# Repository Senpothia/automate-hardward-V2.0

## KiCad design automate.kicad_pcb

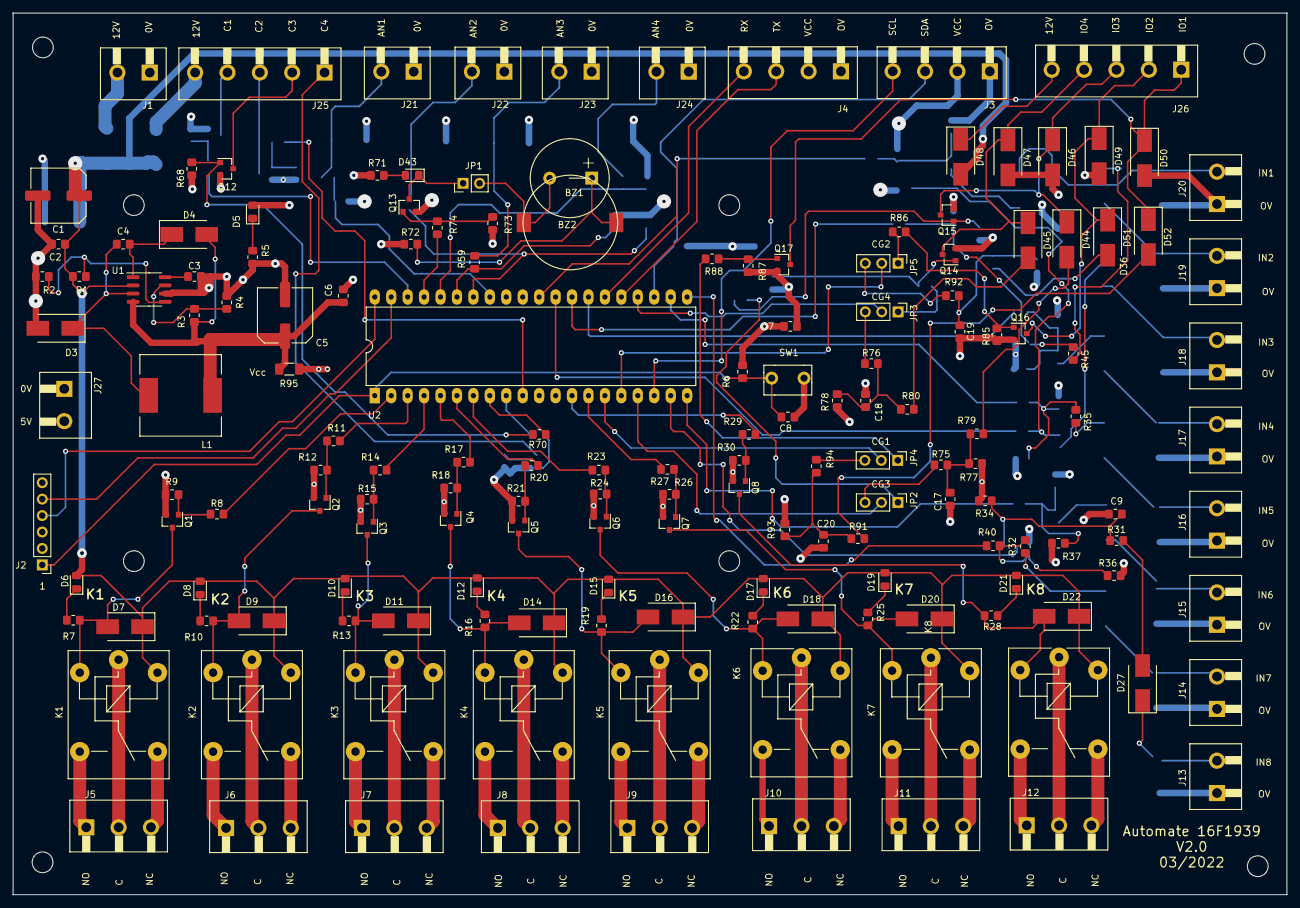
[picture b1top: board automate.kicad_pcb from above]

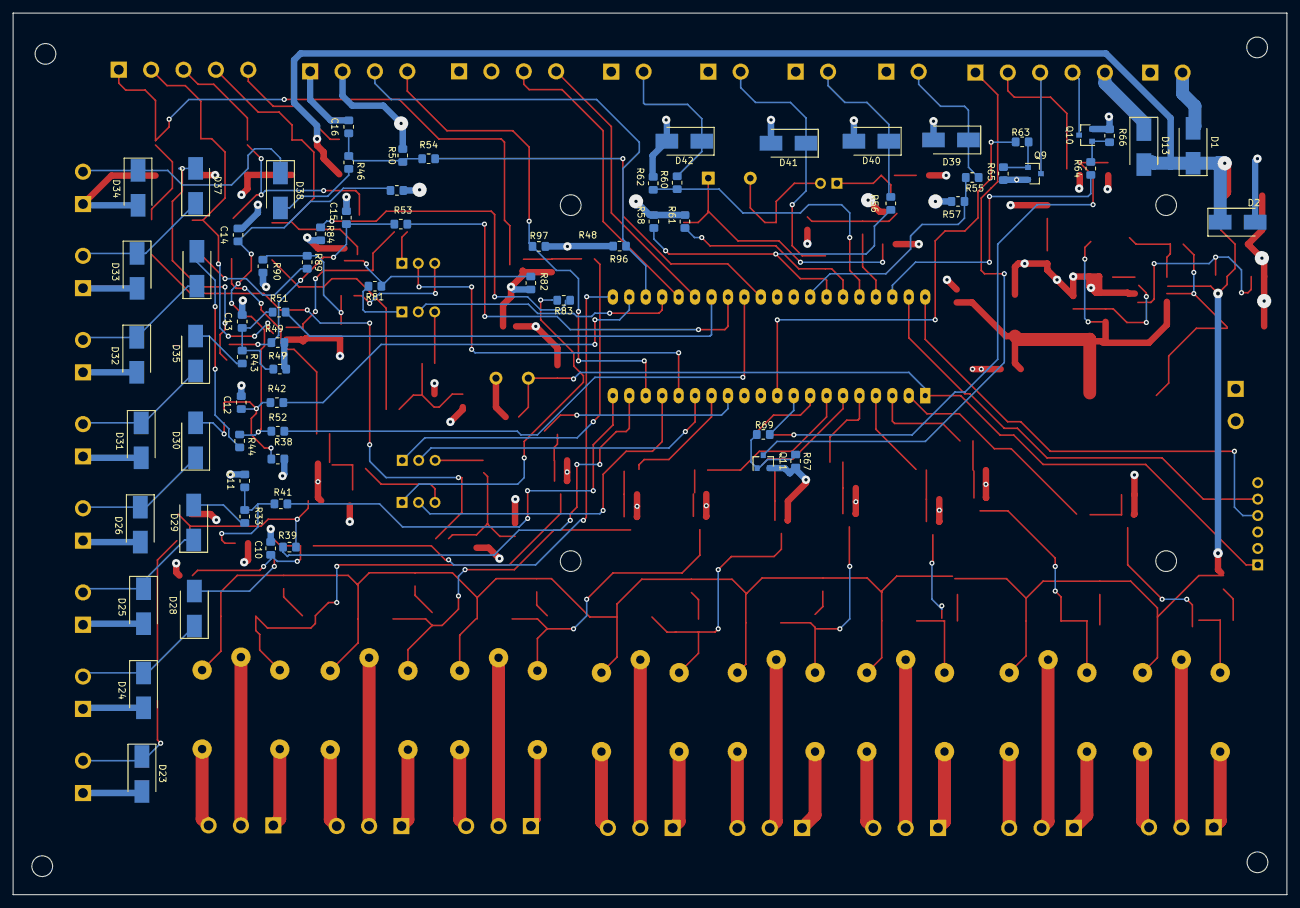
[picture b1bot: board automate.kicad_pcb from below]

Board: 4 copper layers, 196.8 x 136.2 mm, 232 parts (69 on the bottom side), 162 nets.

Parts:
BZ1: Buzzer; Buzzer_Mallory_AST1109MLTRQ
BZ2: Buzzer; Buzzer_12x9.5RM7.6
C1, C5: 100µF; C_Elec_8x6.2
C2, C4, C6, C7, C8, C9, C10, C11, C12, C13, C14, C15, C16, C17, C18, C19, C20: 100nF; R_0805_2012Metric_Pad1.20x1.40mm_HandSolder
C3: 2.2nF; R_0805_2012Metric_Pad1.20x1.40mm_HandSolder
D1, D3, D4, D7, D9, D11, D13, D14, D16, D18, D20, D22, D27, D28, D29, D30, D35, D36, D37, D38, D44, D45, D48, D51, D52: SSA36; D_SMB_SSA36-Handsoldering
D2, D23, D24, D25, D26, D31, D32, D33, D34, D39, D40, D41, D42, D46, D47, D49, D50: SMBJ15A; D_SMB_Handsoldering
D5, D6, D8, D10, D12, D15, D17, D19, D21: LED; D_0805_2012Metric_Pad1.15x1.40mm_HandSolder
D43: LED; LED_0805_2012Metric_Pad1.15x1.40mm_HandSolder
J1, J13, J14, J15, J16, J17, J18, J19, J20, J21, J22, J23, J24, J27: Conn_01x02_Female; conn-2pts-P5mm
J2: Conn_01x06_Female; PinHeader_1x06_P2.54mm_Vertical
J3, J4: Conn_01x04_Female; conn-4pts-P5mm
J5, J6, J7, J8, J9, J10, J11, J12: Conn_01x03_Female; conn-3pts-P5mm
J25, J26: Conn_01x05_Female; conn-5pts-P5mm
JP1: Jumper; PinHeader_1x02_P2.54mm_Vertical
JP2, JP3, JP4, JP5: Jumper_NC_Dual; PinHeader_1x03_P2.54mm_Vertical
K1, K2, K3, K4, K5, K6, K7, K8: SONGLE; Relay_SRD_Series_Form_C
L1: 100µH; L_Wuerth_WE-PD-Typ-LS-12x12
Q1, Q2, Q3, Q4, Q5, Q6, Q7, Q8, Q9, Q10, Q11, Q12, Q13, Q14, Q15, Q16, Q17: BC817; SOT-23.-BC817kicad_mod
R1, R2, R6, R9, R12, R15, R18, R21, R24, R27, R30, R34, R36, R37, R38, R47, R48, R49, R50, R65, R66, R67, R68, R73, R77, R78, R82, R84, R85, R87, R90, R93: 10k; R_0805_2012Metric_Pad1.20x1.40mm_HandSolder
R3: 5.36k; R_0805_2012Metric_Pad1.20x1.40mm_HandSolder
R4: 4.99k; R_0805_2012Metric_Pad1.20x1.40mm_HandSolder
R5, R71: 680; R_0805_2012Metric_Pad1.20x1.40mm_HandSolder
R7, R10, R13, R16, R19, R22, R25, R28: 2.2k; R_0805_2012Metric_Pad1.20x1.40mm_HandSolder
R8, R11, R14, R17, R20, R23, R26, R29, R31, R32, R33, R35, R39, R40, R41, R42, R43, R44, R45, R46, R51, R52, R53, R54, R63, R64, R69, R70, R74, R75, R76, R79, R80, R81, R83, R86, R88, R89, R91, R92, R94, R96, R97: 1k; R_0805_2012Metric_Pad1.20x1.40mm_HandSolder
R55, R56, R59, R60: 8.1k; R_0805_2012Metric_Pad1.20x1.40mm_HandSolder
R57, R58, R61, R62: 4.7k; R_0805_2012Metric_Pad1.20x1.40mm_HandSolder
R72: 0; R_0805_2012Metric_Pad1.20x1.40mm_HandSolder
R95: 0; R_1206_3216Metric_Pad1.30x1.75mm_HandSolder
SW1: SW_Push; SW_PUSH_6mm_H5mm
U1: LT1376CS8TR; SOIC-8_3.9x4.9mm_P1.27mm
U2: PIC16F1939-PDIP40; DIP-40_W15.24mm_LongPads

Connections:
+12V: C1.1, C2.1, D1.2 (A), D2.1 (A1), D6.2 (A), D7.2 (A), D8.2 (A), D9.2 (A), D10.2 (A), D11.2 (A), D12.2 (A), D13.1 (K), D14.2 (A), D15.2 (A), D16.2 (A), D17.2 (A), D18.2 (A), D19.2 (A), D20.2 (A), D21.2 (A), D22.2 (A), D48.1 (K), K1.A1, K2.A1, K3.A1, K4.A1, K5.A1, K6.A1, K7.A1, K8.A1, R1.1, U1.2 (VIN)
/Logique/Vpp: C8.1, J2.1, R6.2, SW1.2, U2.1 (RE3/MCLR/Vpp)
AN1: R55.1, R57.1, U2.33 (RB0/AN12/CPS0/SRI/INT/SEG0)
AN2: R56.1, R58.1, U2.34 (RB1/AN10/C12IN3-/CPS1/VLCD1)
AN3: R59.1, R61.1, U2.35 (RB2/AN8/CPS2/VLCD2)
AN4: R60.1, R62.1, U2.36 (RB3/AN9/C12IN2-/CPS3/CCP2/P2A/VLCD3)
C1: R64.2, U2.38 (RB5/AN13/CPS5/CCP3/P3A/T1G/COM1)
C2: R63.2, U2.10 (SEG23/CCP5/AN7/RE2)
C3: R69.2, U2.9 (SEG22/P3B/AN6/RE1)
C4: R70.2, U2.8 (SEG21/P3A/CCP3/AN5/RE0)
GND: C1.2, C2.2, C3.2, C5.2, C6.2, C7.1, C8.2, C9.2, C10.2, C11.2, C12.2, C13.2, C14.2, C15.2, C16.2, C17.2, C18.2, C19.2, C20.2, D2.2 (A2), D3.1 (K), D23.2 (A2), D24.2 (A2), D25.2 (A2), D26.2 (A2), D31.2 (A2), D32.2 (A2), D33.2 (A2), D34.2 (A2), D39.2 (A2), D40.2 (A2), D41.2 (A2), D42.2 (A2), D46.2 (A2), D47.2 (A2), D49.2 (A2), D50.2 (A2), J1.1, J2.3, J3.1, J4.1, J13.1, J14.1, J15.1, J16.1, J17.1, J18.1, J19.1, J20.1, J21.1, J22.1, J23.1, J24.1, J27.1, Q1.1 (E), Q2.1 (E), Q3.1 (E), Q4.1 (E), Q5.1 (E), Q6.1 (E), Q7.1 (E), Q8.1 (E), Q9.1 (E), Q10.1 (E), Q11.1 (E), Q12.1 (E), Q13.1 (E), Q14.1 (E), Q15.1 (E), Q16.1 (E), Q17.1 (E), R2.2, R4.2, R5.2, R9.1, R12.1, R15.1, R18.1, R21.1, R24.1, R27.1, R30.1, R57.2, R58.2, R61.2, R62.2, R65.2, R66.2, R67.2, R68.2, R73.2, R82.2, R84.2, R85.2, R87.2, SW1.1, U1.6 (GND), U2.12 (VSS), U2.31 (VSS)
GPIO1: JP4.2, U2.15 (P2B/T1CKI/T1OSO/RC0)
GPIO2: JP5.2, U2.16 (P2A/CCP2/T1OSI/RC1)
GPIO3: JP2.2, U2.17 (SEG3/P1A/CCP1/RC2)
GPIO4: JP3.2, U2.24 (SEG10/SDO/RC5)
IN1: R39.1, U2.19 (COM3/CPS8/RD0)
IN2: R41.1, U2.20 (CCP4/CPS9/RD1)
IN3: R40.1, U2.21 (P2B/CPS10/RD2)
IN4: R42.1, U2.22 (SEG16/P2C/CPS11/RD3)
IN5: R51.1, U2.27 (SEG17/P2D/CPS12/RD4)
IN6: R53.1, U2.28 (SEG18/P1B/CPS13/RD5)
IN7: R52.1, U2.29 (SEG19/P1C/CPS14/RD6)
IN8: R54.1, U2.30 (SEG20/P1D/CPS15/RD7)
unnamed: BZ1.1 (-), BZ2.1 (-), R72.2
unnamed: BZ1.2 (+), BZ2.2 (+), JP1.2
unnamed: C3.1, U1.8 (VC)
unnamed: C4.1, D4.2 (A), U1.1 (BOOST)
unnamed: C4.2, D3.2 (A), L1.1, U1.3 (VSW)
unnamed: C5.1, C6.1, D4.1 (K), L1.2, R3.1, R95.2, U1.4 (BIAS)
unnamed: C9.1, R31.1, R34.1, R39.2
unnamed: C10.1, R32.1, R36.1, R40.2
unnamed: C11.1, R33.1, R37.1, R41.2
unnamed: C12.1, R35.1, R38.1, R42.2
unnamed: C13.1, R43.1, R47.1, R51.2
unnamed: C14.1, R44.1, R48.1, R52.2
unnamed: C15.1, R45.1, R49.1, R53.2
unnamed: C16.1, R46.1, R50.1, R54.2
unnamed: C17.1, R75.2, R77.1, R79.1
unnamed: C18.1, R76.2, R78.1, R80.1
unnamed: C19.1, R89.1, R90.1, R92.2
unnamed: C20.1, R91.1, R93.1, R94.2
unnamed: D1.1 (K), J1.2
unnamed: D5.1 (K), R5.1
unnamed: D6.1 (K), R7.1
unnamed: D7.1 (K), K1.A2, Q1.3 (C), R7.2
unnamed: D8.1 (K), R10.1
unnamed: D9.1 (K), K2.A2, Q2.3 (C), R10.2
unnamed: D10.1 (K), R13.1
unnamed: D11.1 (K), K3.A2, Q3.3 (C), R13.2
unnamed: D12.1 (K), R16.1
unnamed: D13.2 (A), J25.5
unnamed: D14.1 (K), K4.A2, Q4.3 (C), R16.2
unnamed: D15.1 (K), R19.1
unnamed: D16.1 (K), K5.A2, Q5.3 (C), R19.2
unnamed: D17.1 (K), R22.1
unnamed: D18.1 (K), K6.A2, Q6.3 (C), R22.2
unnamed: D19.1 (K), R25.1
unnamed: D20.1 (K), K7.A2, Q7.3 (C), R25.2
unnamed: D21.1 (K), R28.1
unnamed: D22.1 (K), K8.A2, Q8.3 (C), R28.2
unnamed: D23.1 (A1), D27.2 (A), J13.2
unnamed: D24.1 (A1), D28.2 (A), J14.2
unnamed: D25.1 (A1), D29.2 (A), J15.2
unnamed: D26.1 (A1), D30.2 (A), J16.2
unnamed: D27.1 (K), R31.2
unnamed: D28.1 (K), R32.2
unnamed: D29.1 (K), R33.2
unnamed: D30.1 (K), R35.2
unnamed: D31.1 (A1), D35.2 (A), J17.2
unnamed: D32.1 (A1), D36.2 (A), J18.2
unnamed: D33.1 (A1), D37.2 (A), J19.2
unnamed: D34.1 (A1), D38.2 (A), J20.2
unnamed: D35.1 (K), R43.2
unnamed: D36.1 (K), R44.2
unnamed: D37.1 (K), R45.2
unnamed: D38.1 (K), R46.2
unnamed: D39.1 (A1), J21.2, R55.2
unnamed: D40.1 (A1), J22.2, R56.2
unnamed: D41.1 (A1), J23.2, R59.2
unnamed: D42.1 (A1), J24.2, R60.2
unnamed: D43.1 (K), JP1.1, Q13.3 (C)
unnamed: D43.2 (A), R71.2
unnamed: D44.1 (K), R79.2
unnamed: D44.2 (A), D46.1 (A1), J26.3, Q15.3 (C)
unnamed: D45.1 (K), R80.2
unnamed: D45.2 (A), D47.1 (A1), J26.4, Q14.3 (C)
unnamed: D48.2 (A), J26.5
unnamed: D49.1 (A1), D51.2 (A), J26.2, Q16.3 (C)
unnamed: D50.1 (A1), D52.2 (A), J26.1, Q17.3 (C)
unnamed: D51.1 (K), R89.2
unnamed: D52.1 (K), R91.2
unnamed: J2.4, U2.40 (RB7/ICSPDAT/ICDDAT/SEG13)
unnamed: J2.5, U2.39 (RB6/ICSPCLK/ICDCLK/SEG14)
unnamed: J3.3, R96.1, U2.23 (SEG11/T1G/SDA/SDI/RC4)
unnamed: J3.4, R97.1, U2.18 (SEG6/SCLK/SCL/RC3)
unnamed: J4.3, U2.25 (SEG9/CK/TX/RC6)
unnamed: J4.4, U2.26 (SEG8/DT/RX/RC7)
unnamed: J5.1, K1.14
unnamed: J5.2, K1.11
unnamed: J5.3, K1.12
unnamed: J6.1, K2.14
unnamed: J6.2, K2.11
unnamed: J6.3, K2.12
unnamed: J7.1, K3.14
unnamed: J7.2, K3.11
unnamed: J7.3, K3.12
unnamed: J8.1, K4.14
unnamed: J8.2, K4.11
unnamed: J8.3, K4.12
unnamed: J9.1, K5.14
unnamed: J9.2, K5.11
unnamed: J9.3, K5.12
unnamed: J10.1, K6.14
unnamed: J10.2, K6.11
unnamed: J10.3, K6.12
unnamed: J11.1, K7.14
unnamed: J11.2, K7.11
unnamed: J11.3, K7.12
unnamed: J12.1, K8.14
unnamed: J12.2, K8.11
unnamed: J12.3, K8.12
unnamed: J25.1, Q11.3 (C)
unnamed: J25.2, Q12.3 (C)
unnamed: J25.3, Q9.3 (C)
unnamed: J25.4, Q10.3 (C)
unnamed: JP2.1, R83.2
unnamed: JP2.3, R75.1
unnamed: JP3.1, R81.2
unnamed: JP3.3, R76.1
unnamed: JP4.1, R88.2
unnamed: JP4.3, R94.1
unnamed: JP5.1, R86.2
unnamed: JP5.3, R92.1
unnamed: Q1.2 (B), R8.1, R9.2
unnamed: Q2.2 (B), R11.1, R12.2
unnamed: Q3.2 (B), R14.1, R15.2
unnamed: Q4.2 (B), R17.1, R18.2
unnamed: Q5.2 (B), R20.1, R21.2
unnamed: Q6.2 (B), R23.1, R24.2
unnamed: Q7.2 (B), R26.1, R27.2
unnamed: Q8.2 (B), R29.1, R30.2
unnamed: Q9.2 (B), R63.1, R65.1
unnamed: Q10.2 (B), R64.1, R66.1
unnamed: Q11.2 (B), R67.1, R69.1
unnamed: Q12.2 (B), R68.1, R70.1
unnamed: Q13.2 (B), R73.1, R74.1
unnamed: Q14.2 (B), R81.1, R82.1
unnamed: Q15.2 (B), R83.1, R84.1
unnamed: Q16.2 (B), R85.1, R86.1
unnamed: Q17.2 (B), R87.1, R88.1
unnamed: R1.2, R2.1, U1.5 (*SHDN)
unnamed: R3.2, R4.1, U1.7 (FB/SENSE)
unnamed: R74.2, U2.37 (RB4/AN11/CPS4/COM0)
Rel1: R8.2, U2.2 (RA0/AN0/C12IN0-/C2OUT/SRNQ/SS/VCAP/SEG12)
Rel2: R11.2, U2.3 (RA1/AN1/C12IN1-/SEG7)
Rel3: R14.2, U2.4 (RA2/AN2/C2IN+/Vref-/DACOUT/COM2)
Rel4: R17.2, U2.5 (RA3/AN3/C1IN+/Vref+/SEG15)
Rel5: R20.2, U2.6 (RA4/C1OUT/CPS6/T0CKI/SRQ/SEG4)
Rel6: R23.2, U2.7 (RA5/AN4/C2OUT/CPS7/SRNQ/SS/VCAP/SEG5)
Rel7: R26.2, U2.14 (RA6/OSC2/CLKOUT/VCAP/SEG1)
Rel8: R29.2, U2.13 (RA7/OSC1/CLKIN/SEG2)
VCC: C7.2, D5.2 (A), J2.2, J3.2, J4.2, J27.2, R6.1, R34.2, R36.2, R37.2, R38.2, R47.2, R48.2, R49.2, R50.2, R71.1, R72.1, R77.2, R78.2, R90.2, R93.2, R95.1, R96.2, R97.2, U2.11 (VDD), U2.32 (VDD)

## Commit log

2022-03-08 hardware version 2.0
2022-03-09 modification position L1, correction sérigraphie
